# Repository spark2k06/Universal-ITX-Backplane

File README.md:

# Universal ITX BackPlane

This backplane is initially intended to be used with Sergey Kiselev's Micro8088 or xi8088 PC clones, among others system powered by x86 architecture. However, other old systems could also be developed using FPGAs built or adapted to ISA or PC / 104 type slots, plus other accessories based on these.

More information of this project in my Hackaday account: https://hackaday.io/project/175340-universal-itx-backplane

The PCB has several I / O connectors common to all projects:

* VGA + MonochromeVGA integrated
* 2 x DB9 ports to be used as serial ports or as joysticks

Additionally, each project can also add a Hat I / O board by adding other specific connectors. For example, an old PC based on a PC / 104 slot could add PS / 2 ports, IDE44 2.0mm connector to connect an external HD or CF, etc ... it must be taken into account that internally the Hat I / O board does not have of a lot of space, several holes have been placed to fasten it to the backplane.

Notice: The project is still in the prototype phase, the first version has not yet been tested.

# Version 1.0

First version of project

Coworked with @MonotechPCs (Twitter profile)

* 4 Layer Mini-ITX board
* 3 x ISA 8 / 16 bits slots
* 1 x PC104 8 / 16 bits slot
* 3 x ISA 8 bits slots
* I/O shield with MonochromeVGA integrated, VGA, and 2 x DB9 connectors

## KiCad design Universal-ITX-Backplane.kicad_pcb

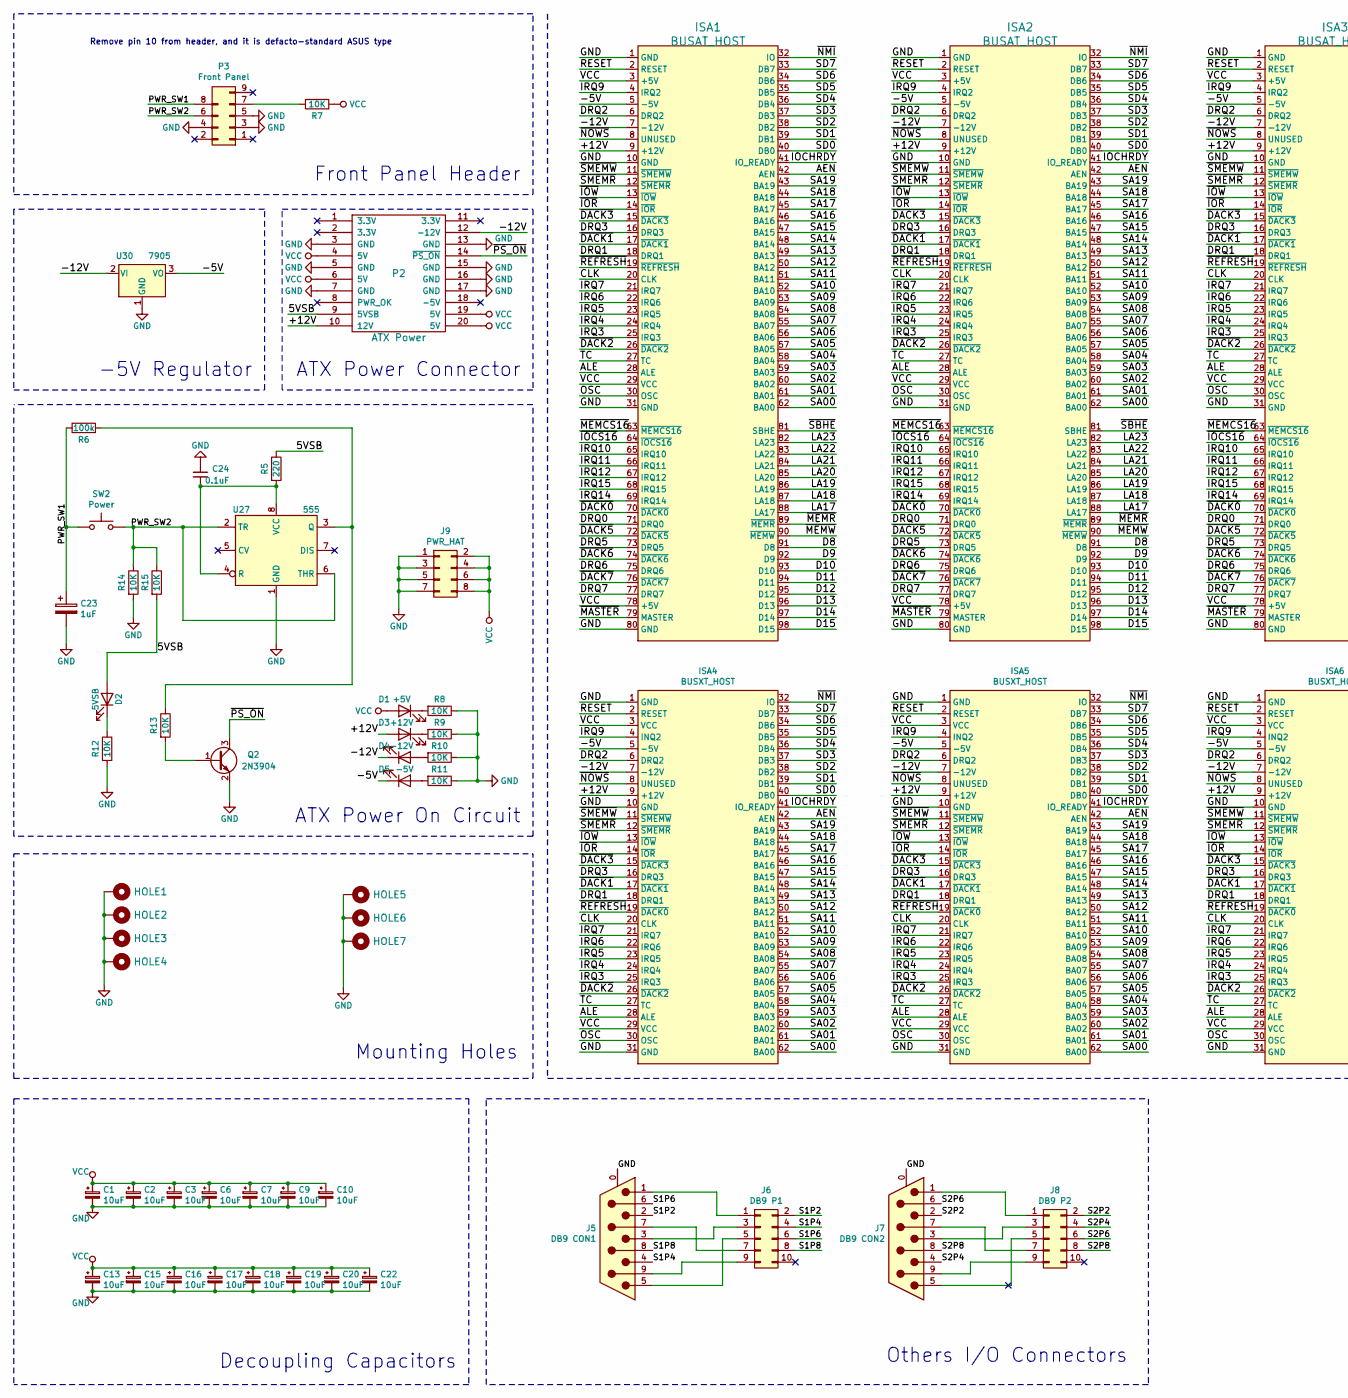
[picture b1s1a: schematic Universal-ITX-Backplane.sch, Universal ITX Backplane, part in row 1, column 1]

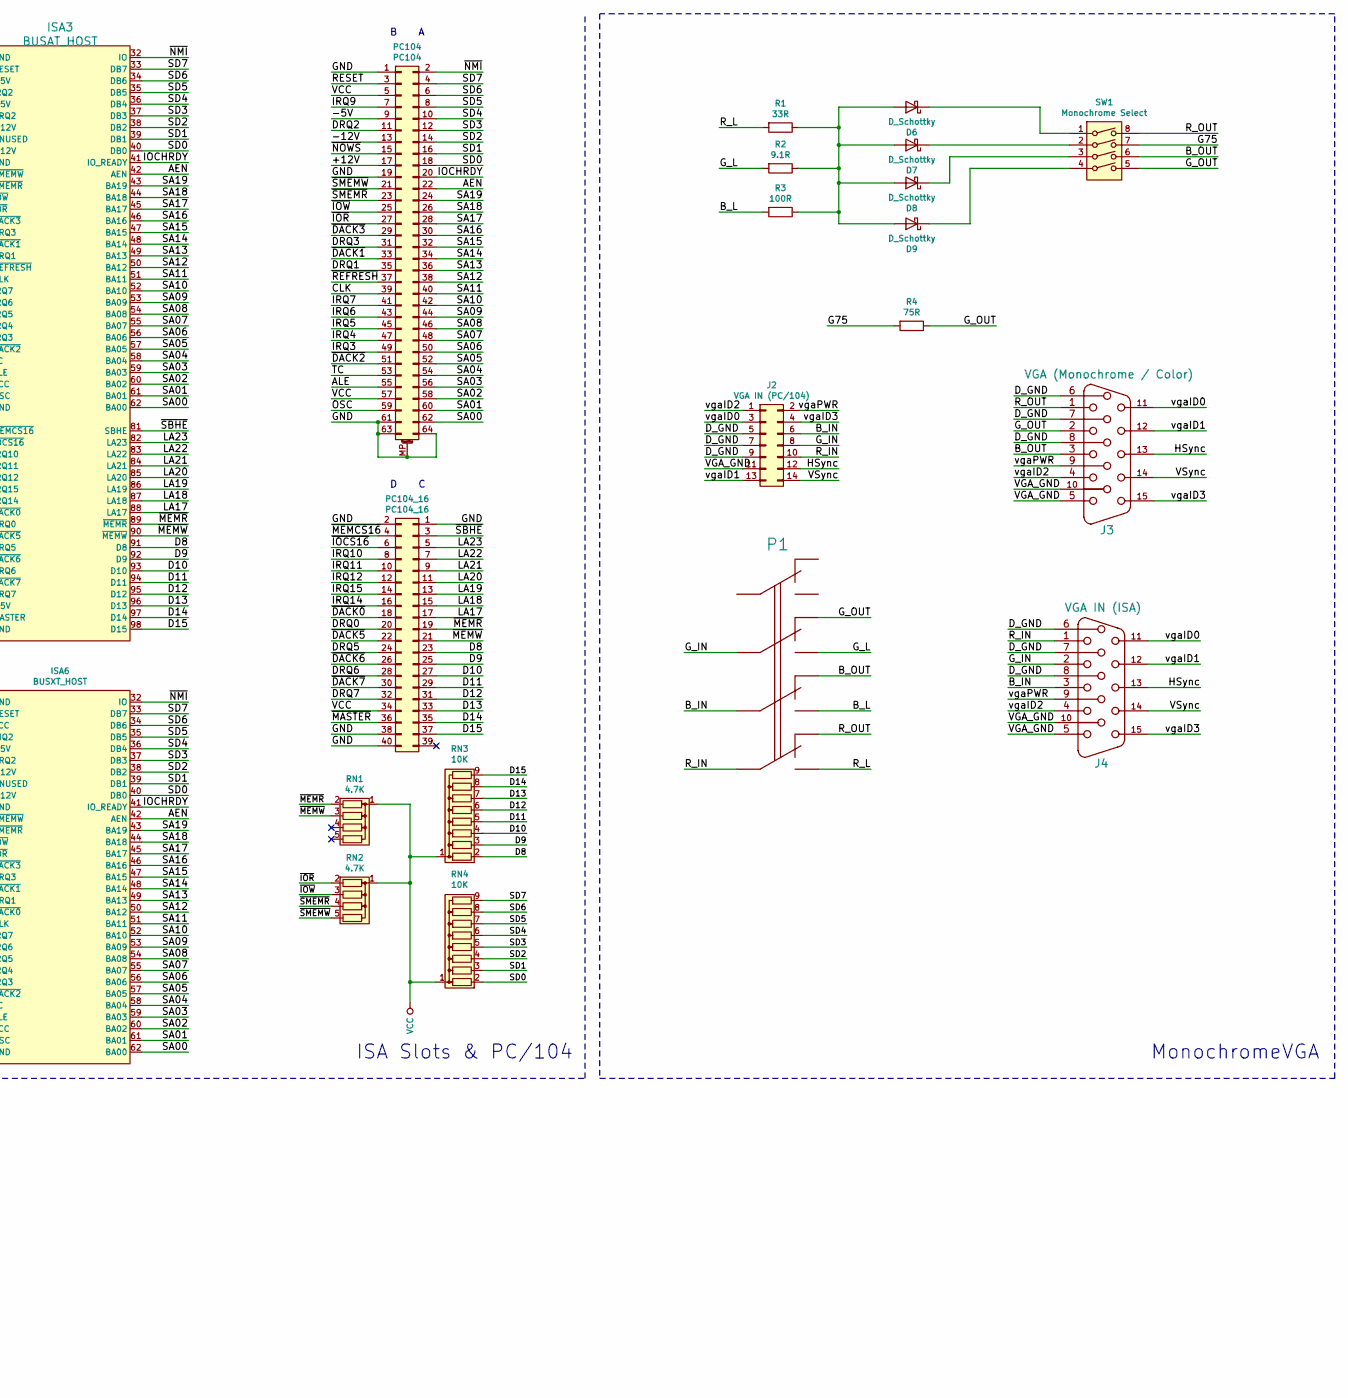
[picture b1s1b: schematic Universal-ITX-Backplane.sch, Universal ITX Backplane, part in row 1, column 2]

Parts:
C1, C2, C3, C6, C7, C9, C10, C13, C15, C16, C17, C18, C19, C20, C22: 10uF; C_Disc_D4.3mm_W1.9mm_P5.00mm; LCSC P# C19702
C23: 1uF; C_Disc_D4.3mm_W1.9mm_P5.00mm; LCSC P# C28323
C24: 0.1uF; C_Disc_D4.3mm_W1.9mm_P5.00mm; LCSC P# C14663
D1: +5V; LED_D3.0mm; LCSC P# C84256
D2: 5VSB; LED_D3.0mm; LCSC P# C84256
D3: +12V; LED_D3.0mm; LCSC P# C84256
D4: -12V; LED_D3.0mm; LCSC P# C84256
D5: -5V; LED_D3.0mm; LCSC P# C84256
D6, D7, D8, D9: D_Schottky; D_DO-35_SOD27_P7.62mm_Horizontal
HOLE1, HOLE2, HOLE3, HOLE4: HOLE; MountingHole_4mm_Pad_Via
HOLE5, HOLE6, HOLE7: HOLE; MountingHole_3.2mm_M3_Pad_Via
ISA1, ISA2, ISA3: BUSAT_HOST; ISA16
ISA4, ISA5, ISA6: BUSXT_HOST; Conn_Edge_ISA8_Longpads
J2: VGA IN (PC/104); PinSocket_2x07_P2.54mm_Vertical
J3: VGA (Monochrome / Color); DSUB-15-HD_Female_Horizontal_P2.29x1.98mm_EdgePinOffset8.35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
J4: VGA IN (ISA); DSUB-15-HD_Female_Vertical_P2.29x1.98mm_MountingHoles
J5: DB9 CON1; DSUB-9_Male_Horizontal_P2.77x2.84mm_EdgePinOffset4.94mm_Hou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
J6: DB9 P1; IDC-Header_2x05_P2.54mm_Vertical
J7: DB9 CON2; DSUB-9_Male_Horizontal_P2.77x2.84mm_EdgePinOffset4.94mm_Hou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
J8: DB9 P2; IDC-Header_2x05_P2.54mm_Vertical
J9: PWR_HAT; PinHeader_2x04_P2.54mm_Vertical
P1: MONO <-> COLOR; SW-SK-42D01-G
P2: ATX Power; Molex_Mini-Fit_Jr_5569-20A2_2x10_P4.20mm_Horizontal
P3: Front Panel; PinHeader_2x05_P2.54mm_Horizontal
PC104: PC104; PC104_Platform
PC104_16: PC104_16; PinSocket_2x20_P2.54mm_Vertical
Q2: 2N3904; TO-92; LCSC P# C20526
R1: 33R; R_Axial_DIN0204_L3.6mm_D1.6mm_P5.08mm_Horizontal
R2: 9.1R; R_Axial_DIN0204_L3.6mm_D1.6mm_P5.08mm_Horizontal
R3: 100R; R_Axial_DIN0204_L3.6mm_D1.6mm_P5.08mm_Horizontal
R4: 75R; R_Axial_DIN0204_L3.6mm_D1.6mm_P5.08mm_Horizontal
R5: 220; R_Axial_DIN0204_L3.6mm_D1.6mm_P5.08mm_Horizontal; LCSC P# C17407
R6: 100k; R_Axial_DIN0204_L3.6mm_D1.6mm_P5.08mm_Horizontal; LCSC P# C17407
R7: 10K; R_Axial_DIN0204_L3.6mm_D1.6mm_P5.08mm_Horizontal
R8, R9, R10, R11, R12, R13, R14, R15: 10K; R_Axial_DIN0204_L3.6mm_D1.6mm_P5.08mm_Horizontal; LCSC P# C17407
RN1, RN2: 4.7K; R_Array_SIP5
RN3, RN4: 10K; R_Array_SIP9
SW1: Monochrome Select; SW_DIP_SPSTx04_Piano_10.8x11.72mm_W7.62mm_P2.54mm
SW2: Power; SW_PUSH_6mm; LCSC P# C128536
U27: 555; DIP-8_W7.62mm_LongPads; LCSC P# C7593
U30: 7905; TO220-3_Soldertab; LCSC P# C75505

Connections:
/5VSB: D2.2 (A), P2.9 (5VSB), R5.1, R15.2
/+12V: D3.2 (A), ISA1.9 (+12V), ISA2.9 (+12V), ISA3.9 (+12V), ISA4.9 (+12V), ISA5.9 (+12V), ISA6.9 (+12V), P2.10 (12V), PC104.17
/-5V: D5.1 (K), ISA1.5 (-5V), ISA2.5 (-5V), ISA3.5 (-5V), ISA4.5 (-5V), ISA5.5 (-5V), ISA6.5 (-5V), PC104.9, U30.3 (VO)
/-12V: D4.1 (K), ISA1.7 (-12V), ISA2.7 (-12V), ISA3.7 (-12V), ISA4.7 (-12V), ISA5.7 (-12V), ISA6.7 (-12V), P2.12 (-12V), PC104.13, U30.2 (VI)
/AEN: ISA1.42 (AEN), ISA2.42 (AEN), ISA3.42 (AEN), ISA4.42 (AEN), ISA5.42 (AEN), ISA6.42 (AEN), PC104.22
/ALE: ISA1.28 (ALE), ISA2.28 (ALE), ISA3.28 (ALE), ISA4.28 (ALE), ISA5.28 (ALE), ISA6.28 (ALE), PC104.55
/B_IN: J2.6, J4.3, P1.8
/B_L: P1.9, R3.2
/B_OUT: J3.3, P1.7, SW1.6
/CLK: ISA1.20 (CLK), ISA2.20 (CLK), ISA3.20 (CLK), ISA4.20 (CLK), ISA5.20 (CLK), ISA6.20 (CLK), PC104.39
/D8: ISA1.91 (D8), ISA2.91 (D8), ISA3.91 (D8), PC104_16.23, RN3.2 (R1)
/D9: ISA1.92 (D9), ISA2.92 (D9), ISA3.92 (D9), PC104_16.25, RN3.3 (R2)
/D10: ISA1.93 (D10), ISA2.93 (D10), ISA3.93 (D10), PC104_16.27, RN3.4 (R3)
/D11: ISA1.94 (D11), ISA2.94 (D11), ISA3.94 (D11), PC104_16.29, RN3.5 (R4)
/D12: ISA1.95 (D12), ISA2.95 (D12), ISA3.95 (D12), PC104_16.31, RN3.6 (R5)
/D13: ISA1.96 (D13), ISA2.96 (D13), ISA3.96 (D13), PC104_16.33, RN3.7 (R6)
/D14: ISA1.97 (D14), ISA2.97 (D14), ISA3.97 (D14), PC104_16.35, RN3.8 (R7)
/D15: ISA1.98 (D15), ISA2.98 (D15), ISA3.98 (D15), PC104_16.37, RN3.9 (R8)
/DRQ0: ISA1.71 (DRQ0), ISA2.71 (DRQ0), ISA3.71 (DRQ0), PC104_16.20
/DRQ1: ISA1.18 (DRQ1), ISA2.18 (DRQ1), ISA3.18 (DRQ1), ISA4.18 (DRQ1), ISA5.18 (DRQ1), ISA6.18 (DRQ1), PC104.35
/DRQ2: ISA1.6 (DRQ2), ISA2.6 (DRQ2), ISA3.6 (DRQ2), ISA4.6 (DRQ2), ISA5.6 (DRQ2), ISA6.6 (DRQ2), PC104.11
/DRQ3: ISA1.16 (DRQ3), ISA2.16 (DRQ3), ISA3.16 (DRQ3), ISA4.16 (DRQ3), ISA5.16 (DRQ3), ISA6.16 (DRQ3), PC104.31
/DRQ5: ISA1.73 (DRQ5), ISA2.73 (DRQ5), ISA3.73 (DRQ5), PC104_16.24
/DRQ6: ISA1.75 (DRQ6), ISA2.75 (DRQ6), ISA3.75 (DRQ6), PC104_16.28
/DRQ7: ISA1.77 (DRQ7), ISA2.77 (DRQ7), ISA3.77 (DRQ7), PC104_16.32
/D_GND: J2.5, J2.7, J2.9, J3.6, J3.7, J3.8, J4.6, J4.7, J4.8
/G75: R4.2, SW1.7
/G_IN: J2.8, J4.2, P1.5
/G_L: P1.6, R2.2
/G_OUT: J3.2, P1.4, R4.1, SW1.5
/HSync: J2.12, J3.13, J4.13
/IOCHRDY: ISA1.41 (IO_READY), ISA2.41 (IO_READY), ISA3.41 (IO_READY), ISA4.41 (IO_READY), ISA5.41 (IO_READY), ISA6.41 (IO_READY), PC104.20
/IRQ3: ISA1.25 (IRQ3), ISA2.25 (IRQ3), ISA3.25 (IRQ3), ISA4.25 (IRQ3), ISA5.25 (IRQ3), ISA6.25 (IRQ3), PC104.49
/IRQ4: ISA1.24 (IRQ4), ISA2.24 (IRQ4), ISA3.24 (IRQ4), ISA4.24 (IRQ4), ISA5.24 (IRQ4), ISA6.24 (IRQ4), PC104.47
/IRQ5: ISA1.23 (IRQ5), ISA2.23 (IRQ5), ISA3.23 (IRQ5), ISA4.23 (IRQ5), ISA5.23 (IRQ5), ISA6.23 (IRQ5), PC104.45
/IRQ6: ISA1.22 (IRQ6), ISA2.22 (IRQ6), ISA3.22 (IRQ6), ISA4.22 (IRQ6), ISA5.22 (IRQ6), ISA6.22 (IRQ6), PC104.43
/IRQ7: ISA1.21 (IRQ7), ISA2.21 (IRQ7), ISA3.21 (IRQ7), ISA4.21 (IRQ7), ISA5.21 (IRQ7), ISA6.21 (IRQ7), PC104.41
/IRQ9: ISA1.4 (IRQ2), ISA2.4 (IRQ2), ISA3.4 (IRQ2), ISA4.4 (INQ2), ISA5.4 (INQ2), ISA6.4 (INQ2), PC104.7
/IRQ10: ISA1.65 (IRQ10), ISA2.65 (IRQ10), ISA3.65 (IRQ10), PC104_16.8
/IRQ11: ISA1.66 (IRQ11), ISA2.66 (IRQ11), ISA3.66 (IRQ11), PC104_16.10
/IRQ12: ISA1.67 (IRQ12), ISA2.67 (IRQ12), ISA3.67 (IRQ12), PC104_16.12
/IRQ14: ISA1.69 (IRQ14), ISA2.69 (IRQ14), ISA3.69 (IRQ14), PC104_16.16
/IRQ15: ISA1.68 (IRQ15), ISA2.68 (IRQ15), ISA3.68 (IRQ15), PC104_16.14
/LA17: ISA1.88 (LA17), ISA2.88 (LA17), ISA3.88 (LA17), PC104_16.17
/LA18: ISA1.87 (LA18), ISA2.87 (LA18), ISA3.87 (LA18), PC104_16.15
/LA19: ISA1.86 (LA19), ISA2.86 (LA19), ISA3.86 (LA19), PC104_16.13
/LA20: ISA1.85 (LA20), ISA2.85 (LA20), ISA3.85 (LA20), PC104_16.11
/LA21: ISA1.84 (LA21), ISA2.84 (LA21), ISA3.84 (LA21), PC104_16.9
/LA22: ISA1.83 (LA22), ISA2.83 (LA22), ISA3.83 (LA22), PC104_16.7
/LA23: ISA1.82 (LA23), ISA2.82 (LA23), ISA3.82 (LA23), PC104_16.5
/OSC: ISA1.30 (OSC), ISA2.30 (OSC), ISA3.30 (OSC), ISA4.30 (OSC), ISA5.30 (OSC), ISA6.30 (OSC), PC104.59
/PWR_SW1: C23.1, P3.8, R6.1, SW2.1
/PWR_SW2: P3.6, R14.1, R15.1, SW2.2, U27.2 (TR), U27.6 (THR)
/RESET: ISA1.2 (RESET), ISA2.2 (RESET), ISA3.2 (RESET), ISA4.2 (RESET), ISA5.2 (RESET), ISA6.2 (RESET), PC104.3
/R_IN: J2.10, J4.1, P1.11
/R_L: P1.12, R1.2
/R_OUT: J3.1, P1.10, SW1.8
/S1P2: J5.2, J6.2
/S1P4: J5.4, J6.4
/S1P6: J5.6, J6.6
/S1P8: J5.8, J6.8
/S2P2: J7.2, J8.2
/S2P4: J7.4, J8.4
/S2P6: J7.6, J8.6
/S2P8: J7.8, J8.8
/SA00: ISA1.62 (BA00), ISA2.62 (BA00), ISA3.62 (BA00), ISA4.62 (BA00), ISA5.62 (BA00), ISA6.62 (BA00), PC104.62
/SA01: ISA1.61 (BA01), ISA2.61 (BA01), ISA3.61 (BA01), ISA4.61 (BA01), ISA5.61 (BA01), ISA6.61 (BA01), PC104.60
/SA02: ISA1.60 (BA02), ISA2.60 (BA02), ISA3.60 (BA02), ISA4.60 (BA02), ISA5.60 (BA02), ISA6.60 (BA02), PC104.58
/SA03: ISA1.59 (BA03), ISA2.59 (BA03), ISA3.59 (BA03), ISA4.59 (BA03), ISA5.59 (BA03), ISA6.59 (BA03), PC104.56
/SA04: ISA1.58 (BA04), ISA2.58 (BA04), ISA3.58 (BA04), ISA4.58 (BA04), ISA5.58 (BA04), ISA6.58 (BA04), PC104.54
/SA05: ISA1.57 (BA05), ISA2.57 (BA05), ISA3.57 (BA05), ISA4.57 (BA05), ISA5.57 (BA05), ISA6.57 (BA05), PC104.52
/SA06: ISA1.56 (BA06), ISA2.56 (BA06), ISA3.56 (BA06), ISA4.56 (BA06), ISA5.56 (BA06), ISA6.56 (BA06), PC104.50
/SA07: ISA1.55 (BA07), ISA2.55 (BA07), ISA3.55 (BA07), ISA4.55 (BA07), ISA5.55 (BA07), ISA6.55 (BA07), PC104.48
/SA08: ISA1.54 (BA08), ISA2.54 (BA08), ISA3.54 (BA08), ISA4.54 (BA08), ISA5.54 (BA08), ISA6.54 (BA08), PC104.46
/SA09: ISA1.53 (BA09), ISA2.53 (BA09), ISA3.53 (BA09), ISA4.53 (BA09), ISA5.53 (BA09), ISA6.53 (BA09), PC104.44
/SA10: ISA1.52 (BA10), ISA2.52 (BA10), ISA3.52 (BA10), ISA4.52 (BA10), ISA5.52 (BA10), ISA6.52 (BA10), PC104.42
/SA11: ISA1.51 (BA11), ISA2.51 (BA11), ISA3.51 (BA11), ISA4.51 (BA11), ISA5.51 (BA11), ISA6.51 (BA11), PC104.40
/SA12: ISA1.50 (BA12), ISA2.50 (BA12), ISA3.50 (BA12), ISA4.50 (BA12), ISA5.50 (BA12), ISA6.50 (BA12), PC104.38
/SA13: ISA1.49 (BA13), ISA2.49 (BA13), ISA3.49 (BA13), ISA4.49 (BA13), ISA5.49 (BA13), ISA6.49 (BA13), PC104.36
/SA14: ISA1.48 (BA14), ISA2.48 (BA14), ISA3.48 (BA14), ISA4.48 (BA14), ISA5.48 (BA14), ISA6.48 (BA14), PC104.34
/SA15: ISA1.47 (BA15), ISA2.47 (BA15), ISA3.47 (BA15), ISA4.47 (BA15), ISA5.47 (BA15), ISA6.47 (BA15), PC104.32
/SA16: ISA1.46 (BA16), ISA2.46 (BA16), ISA3.46 (BA16), ISA4.46 (BA16), ISA5.46 (BA16), ISA6.46 (BA16), PC104.30
/SA17: ISA1.45 (BA17), ISA2.45 (BA17), ISA3.45 (BA17), ISA4.45 (BA17), ISA5.45 (BA17), ISA6.45 (BA17), PC104.28
/SA18: ISA1.44 (BA18), ISA2.44 (BA18), ISA3.44 (BA18), ISA4.44 (BA18), ISA5.44 (BA18), ISA6.44 (BA18), PC104.26
/SA19: ISA1.43 (BA19), ISA2.43 (BA19), ISA3.43 (BA19), ISA4.43 (BA19), ISA5.43 (BA19), ISA6.43 (BA19), PC104.24
/SD0: ISA1.40 (DB0), ISA2.40 (DB0), ISA3.40 (DB0), ISA4.40 (DB0), ISA5.40 (DB0), ISA6.40 (DB0), PC104.18, RN4.2 (R1)
/SD1: ISA1.39 (DB1), ISA2.39 (DB1), ISA3.39 (DB1), ISA4.39 (DB1), ISA5.39 (DB1), ISA6.39 (DB1), PC104.16, RN4.3 (R2)
/SD2: ISA1.38 (DB2), ISA2.38 (DB2), ISA3.38 (DB2), ISA4.38 (DB2), ISA5.38 (DB2), ISA6.38 (DB2), PC104.14, RN4.4 (R3)
/SD3: ISA1.37 (DB3), ISA2.37 (DB3), ISA3.37 (DB3), ISA4.37 (DB3), ISA5.37 (DB3), ISA6.37 (DB3), PC104.12, RN4.5 (R4)
/SD4: ISA1.36 (DB4), ISA2.36 (DB4), ISA3.36 (DB4), ISA4.36 (DB4), ISA5.36 (DB4), ISA6.36 (DB4), PC104.10, RN4.6 (R5)
/SD5: ISA1.35 (DB5), ISA2.35 (DB5), ISA3.35 (DB5), ISA4.35 (DB5), ISA5.35 (DB5), ISA6.35 (DB5), PC104.8, RN4.7 (R6)
/SD6: ISA1.34 (DB6), ISA2.34 (DB6), ISA3.34 (DB6), ISA4.34 (DB6), ISA5.34 (DB6), ISA6.34 (DB6), PC104.6, RN4.8 (R7)
/SD7: ISA1.33 (DB7), ISA2.33 (DB7), ISA3.33 (DB7), ISA4.33 (DB7), ISA5.33 (DB7), ISA6.33 (DB7), PC104.4, RN4.9 (R8)
/TC: ISA1.27 (TC), ISA2.27 (TC), ISA3.27 (TC), ISA4.27 (TC), ISA5.27 (TC), ISA6.27 (TC), PC104.53
/VGA_GND: J2.11, J3.5, J3.10, J4.5, J4.10
/VSync: J2.14, J3.14, J4.14
/vgaID0: J2.3, J3.11, J4.11
/vgaID1: J2.13, J3.12, J4.12
/vgaID2: J2.1, J3.4, J4.4
/vgaID3: J2.4, J3.15, J4.15
/vgaPWR: J2.2, J3.9, J4.9
/~DACK0: ISA1.70 (~DACK0), ISA2.70 (~DACK0), ISA3.70 (~DACK0), PC104_16.18
/~DACK1: ISA1.17 (~DACK1), ISA2.17 (~DACK1), ISA3.17 (~DACK1), ISA4.17 (~DACK1), ISA5.17 (~DACK1), ISA6.17 (~DACK1), PC104.33
/~DACK2: ISA1.26 (~DACK2), ISA2.26 (~DACK2), ISA3.26 (~DACK2), ISA4.26 (~DACK2), ISA5.26 (~DACK2), ISA6.26 (~DACK2), PC104.51
/~DACK3: ISA1.15 (~DACK3), ISA2.15 (~DACK3), ISA3.15 (~DACK3), ISA4.15 (~DACK3), ISA5.15 (~DACK3), ISA6.15 (~DACK3), PC104.29
/~DACK5: ISA1.72 (~DACK5), ISA2.72 (~DACK5), ISA3.72 (~DACK5), PC104_16.22
/~DACK6: ISA1.74 (~DACK6), ISA2.74 (~DACK6), ISA3.74 (~DACK6), PC104_16.26
/~DACK7: ISA1.76 (~DACK7), ISA2.76 (~DACK7), ISA3.76 (~DACK7), PC104_16.30
/~IOCS16: ISA1.64 (~IOCS16), ISA2.64 (~IOCS16), ISA3.64 (~IOCS16), PC104_16.6
/~IOR: ISA1.14 (~IOR), ISA2.14 (~IOR), ISA3.14 (~IOR), ISA4.14 (~IOR), ISA5.14 (~IOR), ISA6.14 (~IOR), PC104.27, RN2.2 (R1)
/~IOW: ISA1.13 (~IOW), ISA2.13 (~IOW), ISA3.13 (~IOW), ISA4.13 (~IOW), ISA5.13 (~IOW), ISA6.13 (~IOW), PC104.25, RN2.3 (R2)
/~MASTER: ISA1.79 (MASTER), ISA2.79 (MASTER), ISA3.79 (MASTER), PC104_16.36
/~MEMCS16: ISA1.63 (~MEMCS16), ISA2.63 (~MEMCS16), ISA3.63 (~MEMCS16), PC104_16.4
/~MEMR: ISA1.89 (~MEMR), ISA2.89 (~MEMR), ISA3.89 (~MEMR), PC104_16.19, RN1.2 (R1)
/~MEMW: ISA1.90 (~MEMW), ISA2.90 (~MEMW), ISA3.90 (~MEMW), PC104_16.21, RN1.3 (R2)
/~NMI: ISA1.32 (IO), ISA2.32 (IO), ISA3.32 (IO), ISA4.32 (IO), ISA5.32 (IO), ISA6.32 (IO), PC104.2
/~NOWS: ISA1.8 (UNUSED), ISA2.8 (UNUSED), ISA3.8 (UNUSED), ISA4.8 (UNUSED), ISA5.8 (UNUSED), ISA6.8 (UNUSED), PC104.15
/~PS_ON: P2.14 (~PS_ON), Q2.3 (C)
/~REFRESH: ISA1.19 (~REFRESH), ISA2.19 (~REFRESH), ISA3.19 (~REFRESH), ISA4.19 (~DACK0), ISA5.19 (~DACK0), ISA6.19 (~DACK0), PC104.37
/~SBHE: ISA1.81 (SBHE), ISA2.81 (SBHE), ISA3.81 (SBHE), PC104_16.3
/~SMEMR: ISA1.12 (~SMEMR), ISA2.12 (~SMEMR), ISA3.12 (~SMEMR), ISA4.12 (~SMEMR), ISA5.12 (~SMEMR), ISA6.12 (~SMEMR), PC104.23, RN2.4 (R3)
/~SMEMW: ISA1.11 (~SMEMW), ISA2.11 (~SMEMW), ISA3.11 (~SMEMW), ISA4.11 (~SMEMW), ISA5.11 (~SMEMW), ISA6.11 (~SMEMW), PC104.21, RN2.5 (R4)
GND: C1.2, C2.2, C3.2, C6.2, C7.2, C9.2, C10.2, C13.2, C15.2, C16.2, C17.2, C18.2, C19.2, C20.2, C22.2, C23.2, C24.2, HOLE1.1, HOLE2.1, HOLE3.1, HOLE4.1, HOLE5.1, HOLE6.1, HOLE7.1, ISA1.1 (GND), ISA1.10 (GND), ISA1.31 (GND), ISA1.80 (GND), ISA2.1 (GND), ISA2.10 (GND), ISA2.31 (GND), ISA2.80 (GND), ISA3.1 (GND), ISA3.10 (GND), ISA3.31 (GND), ISA3.80 (GND), ISA4.1 (GND), ISA4.10 (GND), ISA4.31 (GND), ISA5.1 (GND), ISA5.10 (GND), ISA5.31 (GND), ISA6.1 (GND), ISA6.10 (GND), ISA6.31 (GND), J5.0 (PAD), J7.0 (PAD), J9.1, J9.3, J9.5, J9.7, P2.3 (GND), P2.5 (GND), P2.7 (GND), P2.13 (GND), P2.15 (GND), P2.16 (GND), P2.17 (GND), P3.3, P3.4, P3.5, PC104.1, PC104.19, PC104.61, PC104.63, PC104.64, PC104.MP (MountPin), PC104_16.1, PC104_16.2, PC104_16.38, PC104_16.40, Q2.2 (E), R8.1, R9.1, R10.1, R11.1, R12.2, R14.2, U27.1 (GND), U30.1 (GND)
unnamed: C24.1, R5.2, U27.4 (R), U27.8 (VCC)
unnamed: D1.1 (K), R8.2
unnamed: D2.1 (K), R12.1
unnamed: D3.1 (K), R9.2
unnamed: D4.2 (A), R10.2
unnamed: D5.2 (A), R11.2
unnamed: D6.1 (K), SW1.1
unnamed: D6.2 (A), D7.2 (A), D8.2 (A), D9.2 (A), R1.1, R2.1, R3.1
unnamed: D7.1 (K), SW1.2
unnamed: D8.1 (K), SW1.3
unnamed: D9.1 (K), SW1.4
unnamed: J5.1, J6.1
unnamed: J5.3, J6.3
unnamed: J5.5, J6.5
unnamed: J5.7, J6.7
unnamed: J5.9, J6.9
unnamed: J7.1, J8.1
unnamed: J7.3, J8.3
unnamed: J7.5, J8.5
unnamed: J7.7, J8.7
unnamed: J7.9, J8.9
unnamed: P3.7, R7.2
unnamed: Q2.1 (B), R13.2
unnamed: R6.2, R13.1, U27.3 (Q)
VCC: C1.1, C2.1, C3.1, C6.1, C7.1, C9.1, C10.1, C13.1, C15.1, C16.1, C17.1, C18.1, C19.1, C20.1, C22.1, D1.2 (A), ISA1.3 (+5V), ISA1.29 (VCC), ISA1.78 (+5V), ISA2.3 (+5V), ISA2.29 (VCC), ISA2.78 (+5V), ISA3.3 (+5V), ISA3.29 (VCC), ISA3.78 (+5V), ISA4.3 (VCC), ISA4.29 (VCC), ISA5.3 (VCC), ISA5.29 (VCC), ISA6.3 (VCC), ISA6.29 (VCC), J9.2, J9.4, J9.6, J9.8, P2.4 (5V), P2.6 (5V), P2.19 (5V), P2.20 (5V), PC104.5, PC104.57, PC104_16.34, R7.1, RN1.1 (common), RN2.1 (common), RN3.1 (common), RN4.1 (common)

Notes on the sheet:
ATX Power On Circuit
Remove pin 10 from header, and it is defacto-standard ASUS type
Front Panel Header
Decoupling Capacitors
ATX Power Connector
-5V Regulator
Mounting Holes
D C
B A
MonochromeVGA
ISA Slots & PC/104
Others I/O Connectors

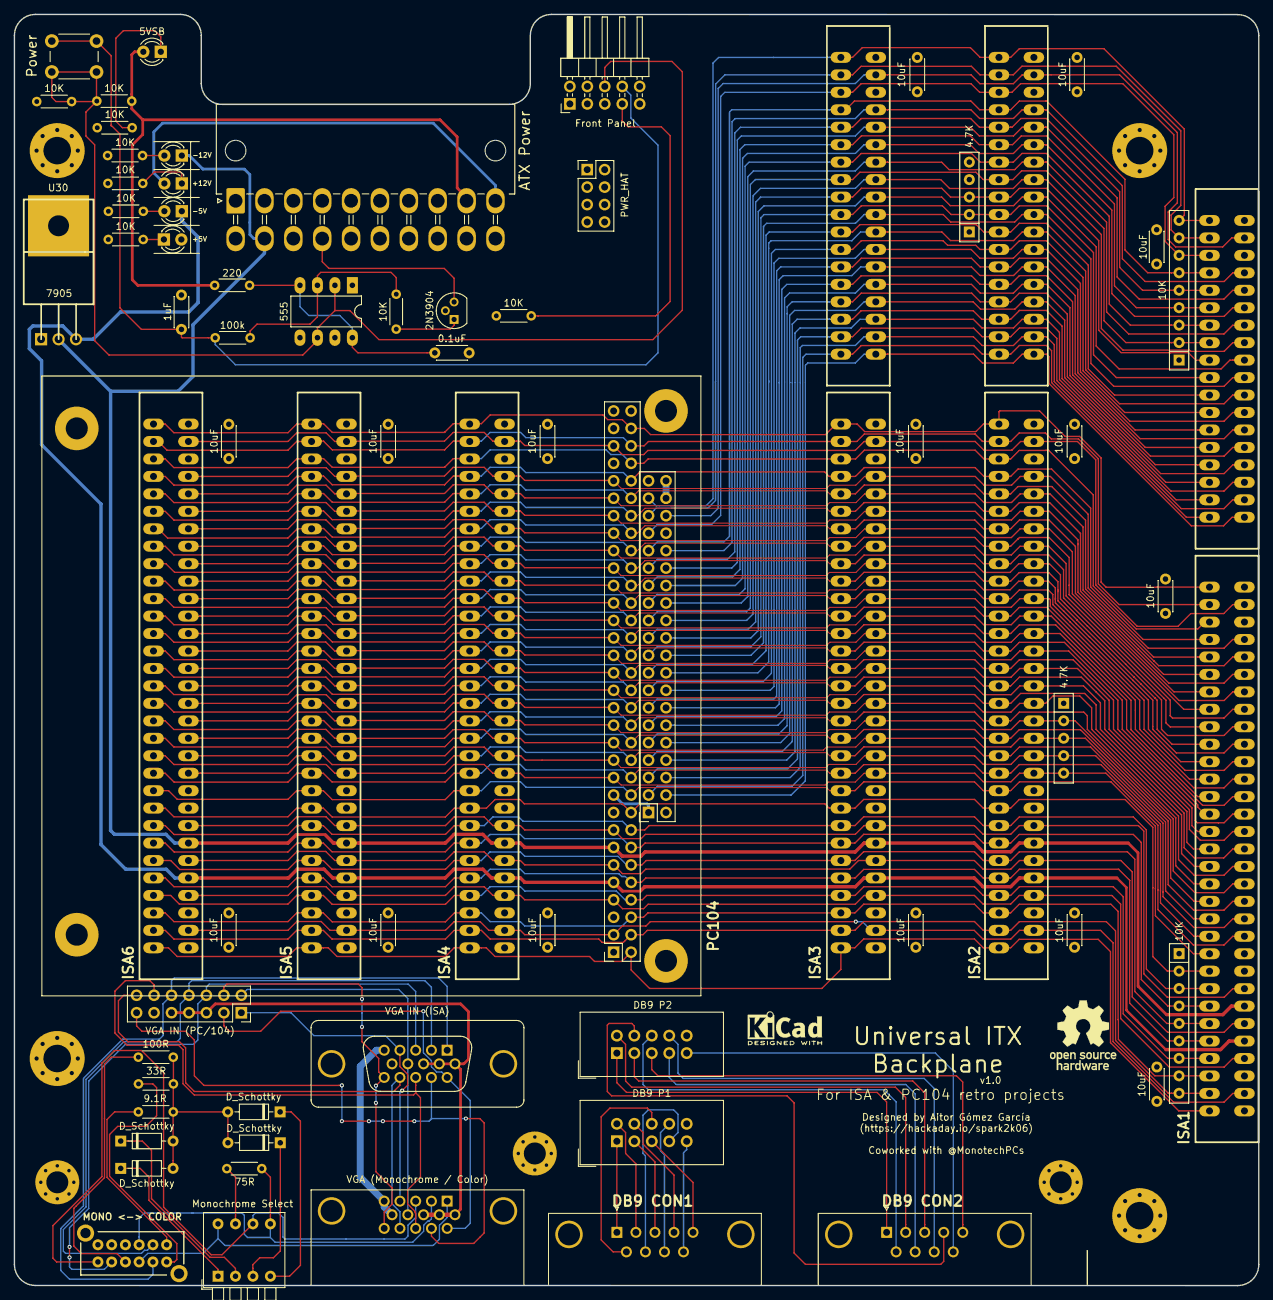
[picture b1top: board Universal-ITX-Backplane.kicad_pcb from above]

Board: 4 copper layers, 181.0 x 184.9 mm, 76 parts (0 on the bottom side), 148 nets.

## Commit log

2020-10-12 Version 1.0
2020-12-18 Update to License CERN, according to open hardware

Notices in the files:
Universal-ITX-Backplane.kicad_pcb:
Aitor Gomez Garcia | License: GFDLv3
